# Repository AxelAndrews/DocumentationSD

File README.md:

# DocumentationSD
Documentation hub for the 2024-2025 Portal Box Senior Design project. Contains instruction guides, reports, diagrams, and other documentation related to the project.

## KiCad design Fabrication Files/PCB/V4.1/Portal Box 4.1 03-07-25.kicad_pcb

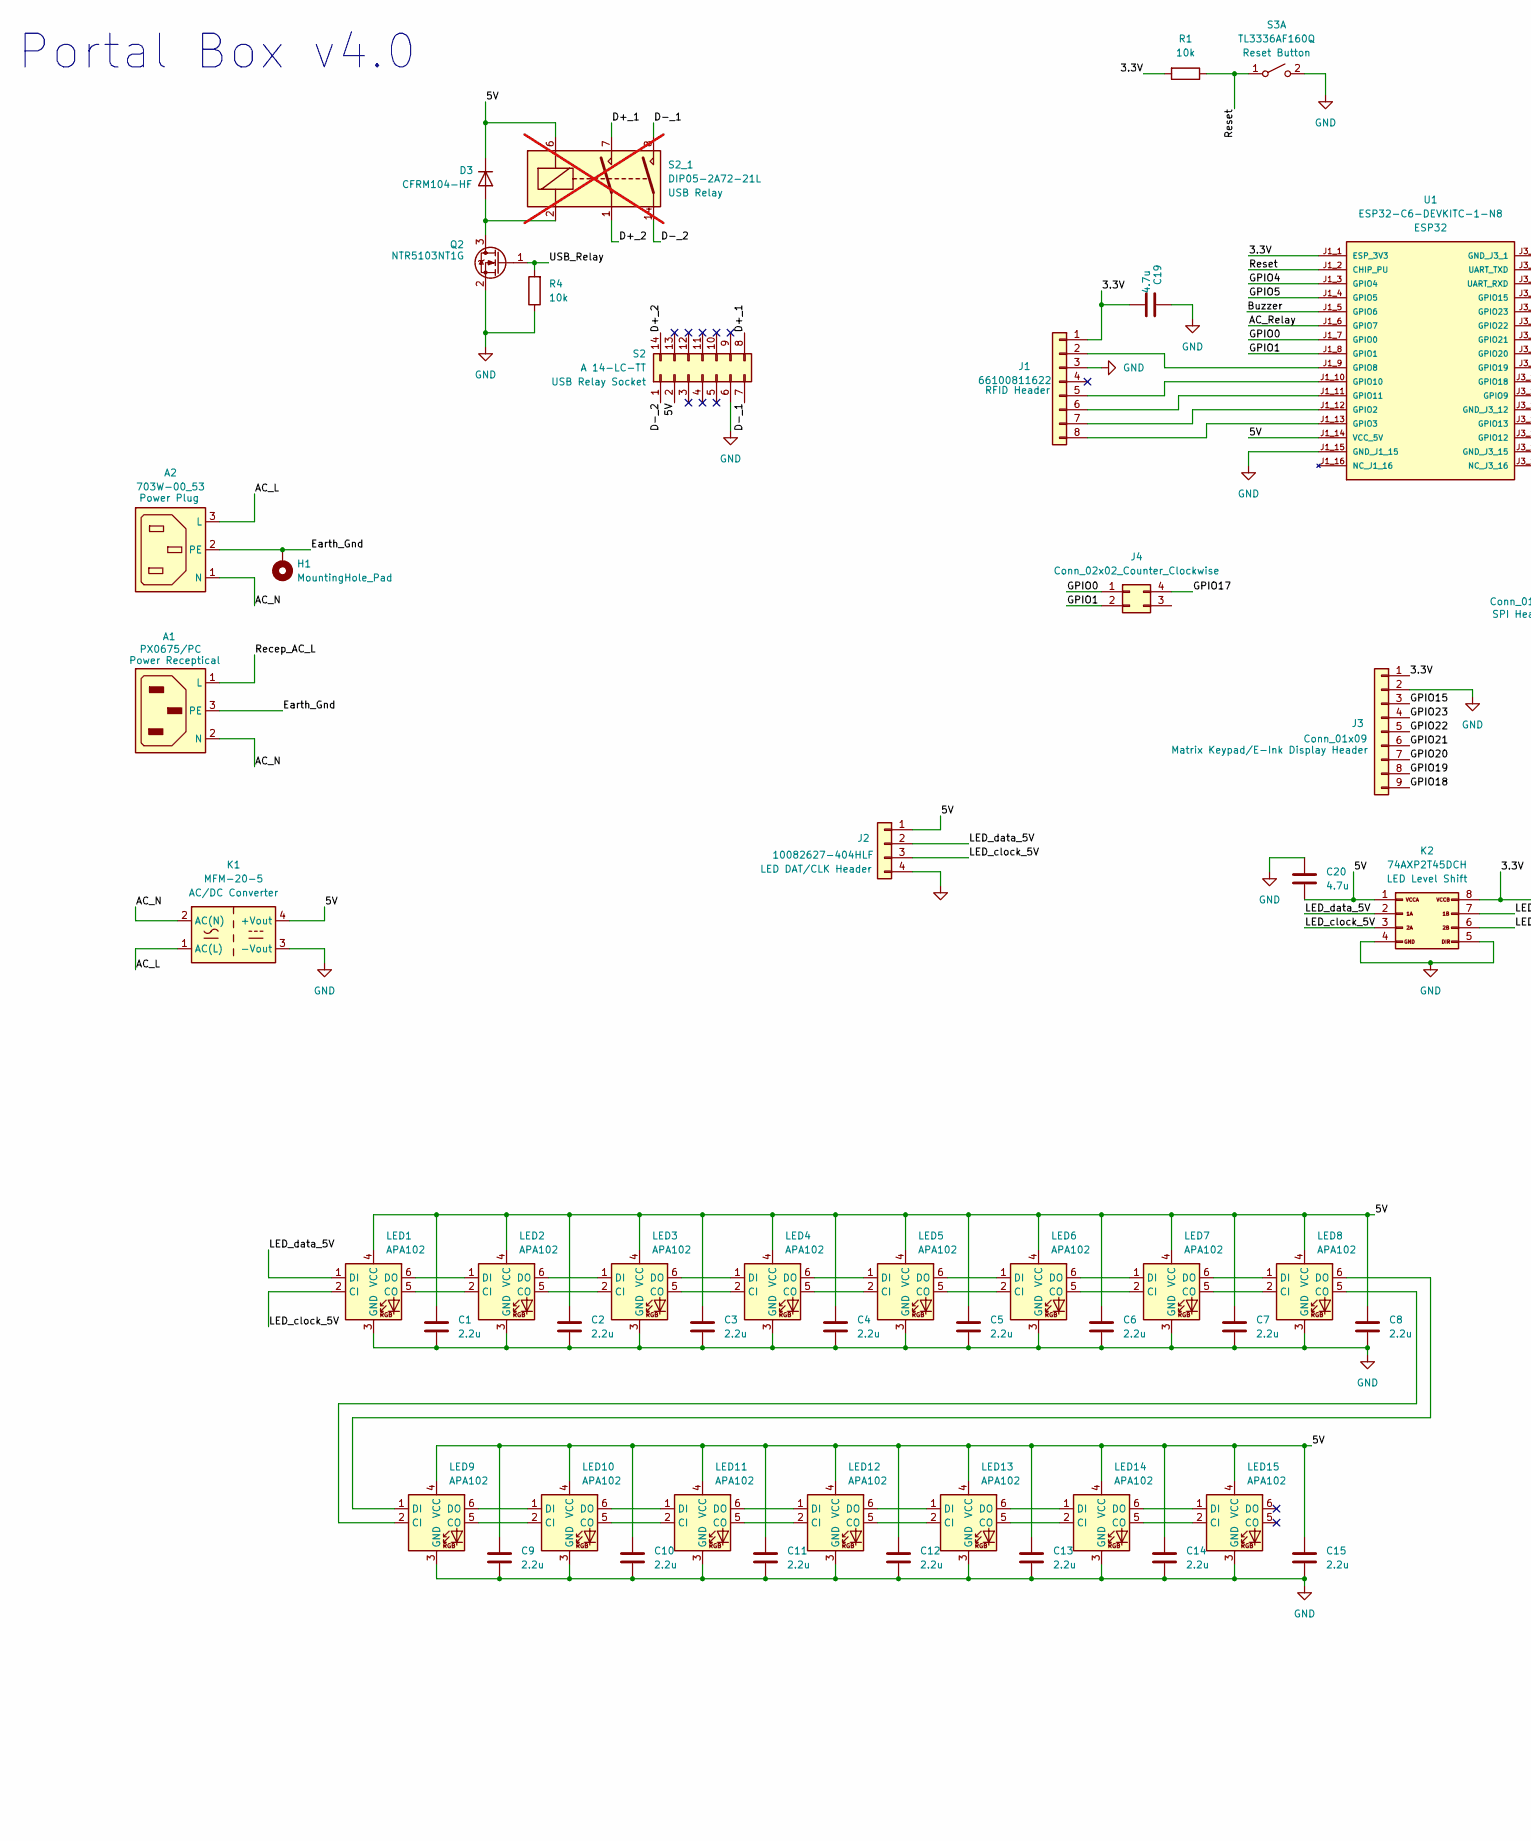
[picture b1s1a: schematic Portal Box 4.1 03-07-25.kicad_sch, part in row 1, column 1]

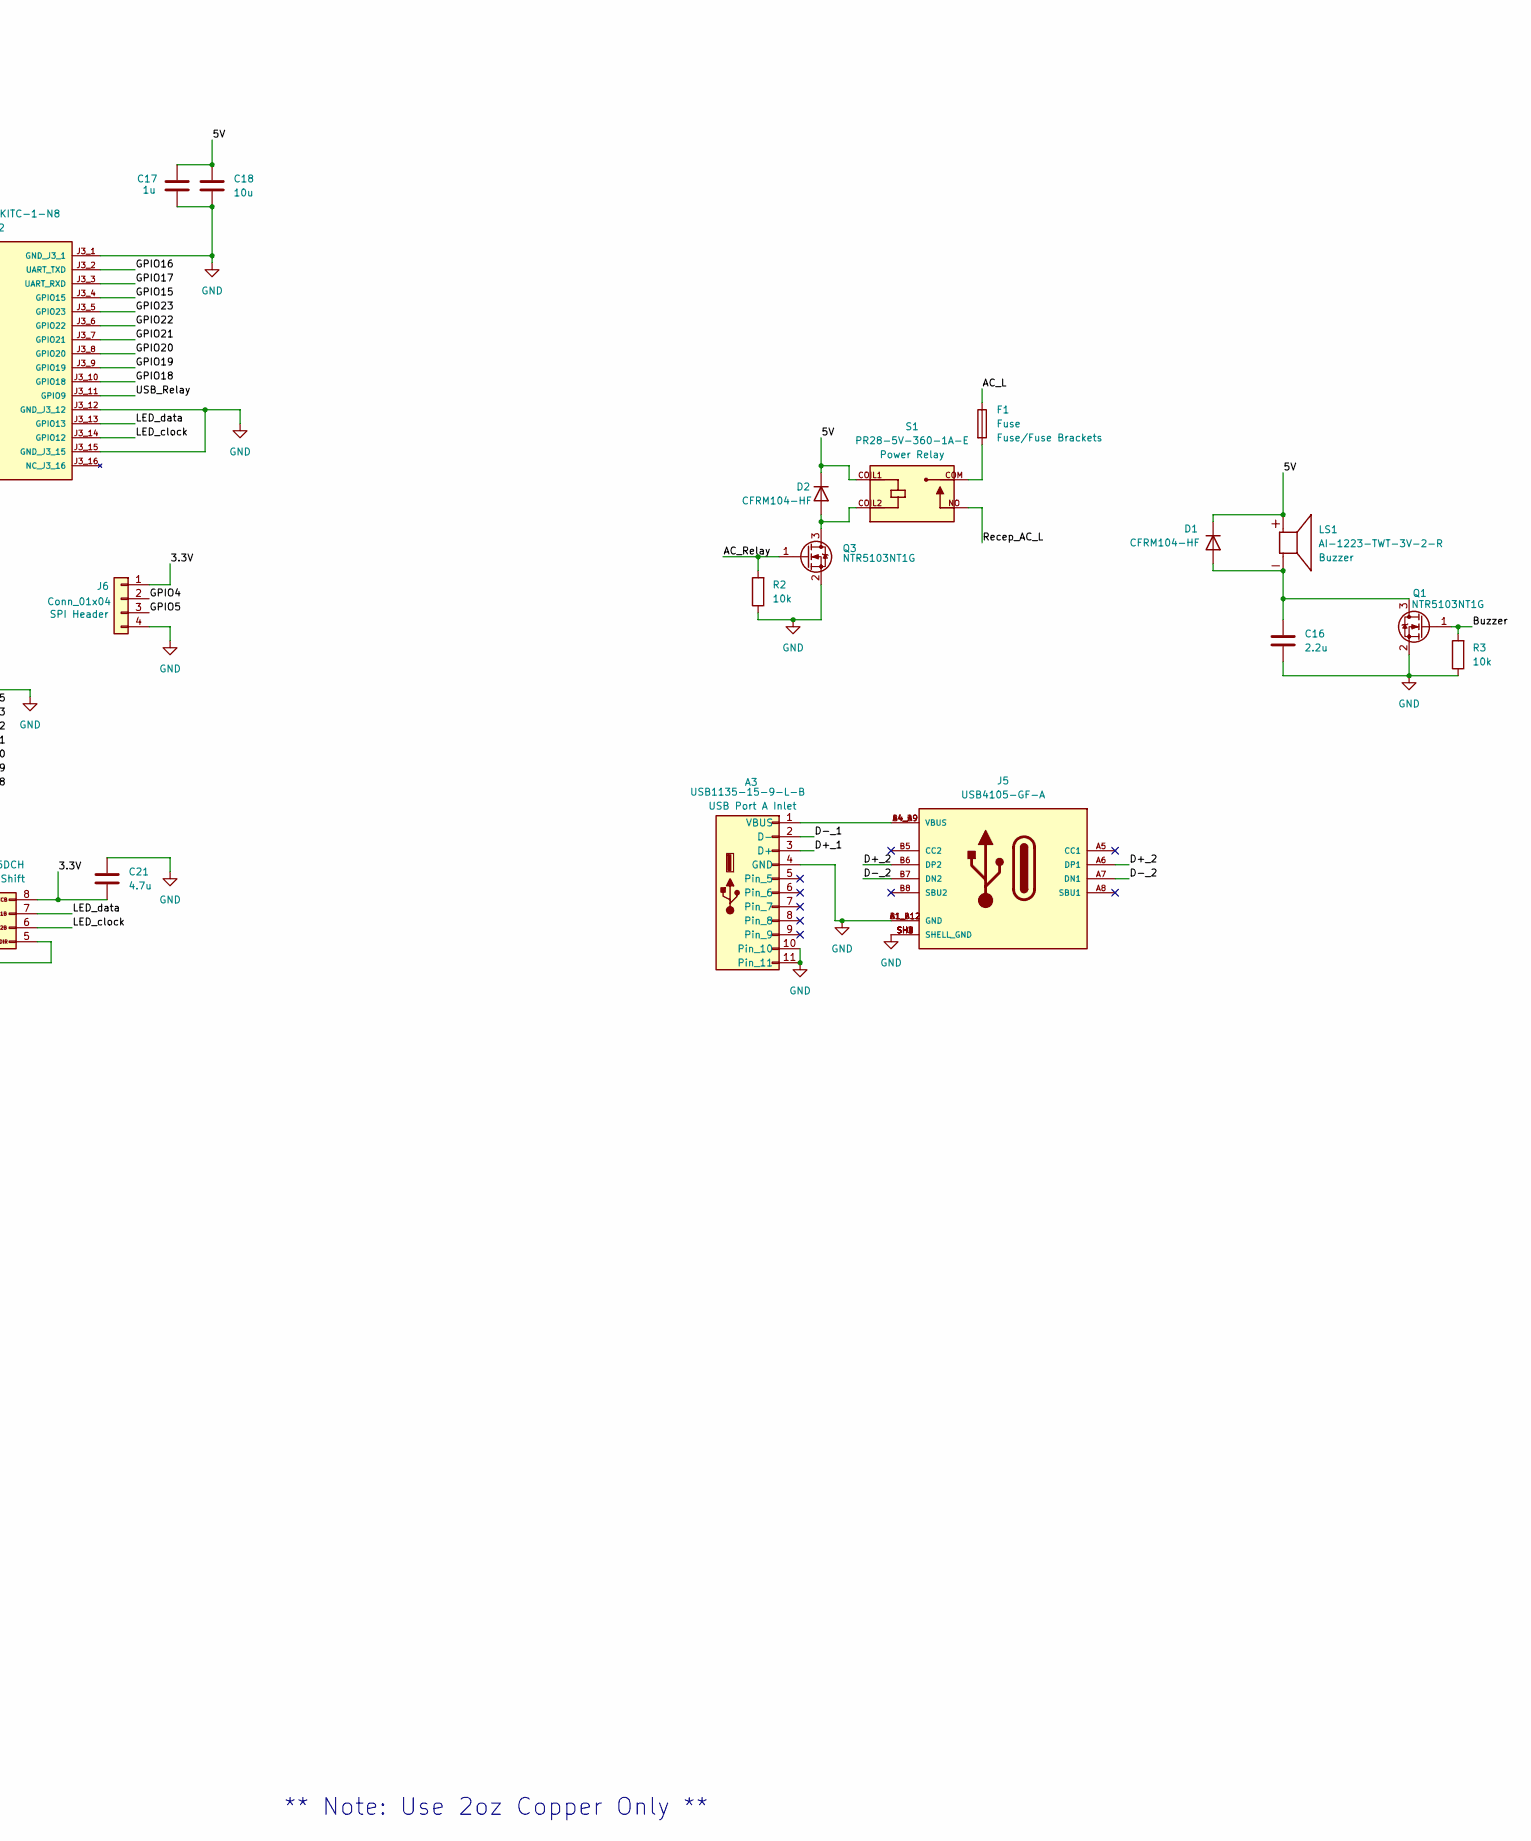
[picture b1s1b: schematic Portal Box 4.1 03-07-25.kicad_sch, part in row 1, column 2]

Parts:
A1: PX0675/PC; BULGIN_PX0675_PC
A2: 703W-00_53; QUALTEK_703W-00_53
A3: USB1135-15-9-L-B; GCT_USB1135-15-9-L-B_REVA1
C1, C2, C3, C4, C5, C6, C7, C8, C9, C10, C11, C12, C13, C14, C15, C16: 2.2u; C_0805_2012Metric
C17: 1u; C_0805_2012Metric
C18: 10u; C_0805_2012Metric
C19, C20, C21: 4.7u; C_0805_2012Metric
D1, D2, D3: CFRM104-HF; D_SOD-123
F1: Fuse; Fuseholder_Clip-5x20mm_Schurter_CQM_Inline_P20.60x5.00mm_D1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
H1: MountingHole_Pad; MountingHole_3.2mm_M3
J1: 66100811622; PinHeader_1x08_P2.54mm_Vertical
J2: 10082627-404HLF; PinHeader_1x04_P2.54mm_Vertical
J3: Conn_01x09; PinHeader_1x09_P2.54mm_Vertical
J4: Conn_02x02_Counter_Clockwise; PinHeader_2x02_P2.54mm_Vertical
J5: USB4105-GF-A; GCT_USB4105-GF-A; PARTREV B4
J6: Conn_01x04; PinHeader_1x04_P2.54mm_Vertical
K1: MFM-20-5; Converter_ACDC_MeanWell_MFM-15-xx_THT
K2: 74AXP2T45DCH; VSSOP8_SOT765-1_NEX
LED1, LED2, LED3, LED4, LED5, LED6, LED7, LED8, LED9, LED10, LED11, LED12, LED13, LED14, LED15: APA102; SK9822_ADA
LS1: AI-1223-TWT-3V-2-R; XDCR_AI-1223-TWT-3V-2-R; PARTREV 3/18/2020; DigiKey_Part_Number 668-1456-ND
Q1, Q2, Q3: NTR5103NT1G; SOT-23
R1, R2, R3, R4: 10k; R_0805_2012Metric
S1: PR28-5V-360-1A-E; RELAY_PR28-5V-360-1A-E; PARTREV 1.01
S2: A 14-LC-TT; DIP-14_W7.62mm
S2_1: DIP05-2A72-21L; Relay_StandexMeder_DIP_LowProfile; not fitted
S3: TL3336AF160Q; SW_TL3336AF160Q
U1: ESP32-C6-DEVKITC-1-N8; MODULE_ESP32-C6-DEVKITC-1-N8; PARTREV 1.3

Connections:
/3.3V: C19.2, C21.2, J1.1, J3.1, J6.1, K2.8 (VCCB), R1.2, U1.J1_1 (ESP_3V3)
/5V: C1.1, C2.1, C3.1, C4.1, C5.1, C6.1, C7.1, C8.1, C9.1, C10.1, C11.1, C12.1, C13.1, C14.1, C15.1, C17.1, C18.1, C20.2, D1.1 (K), D2.1 (K), D3.1 (K), J2.1, K1.4 (+Vout), K2.1 (VCCA), LED1.4 (VCC), LED2.4 (VCC), LED3.4 (VCC), LED4.4 (VCC), LED5.4 (VCC), LED6.4 (VCC), LED7.4 (VCC), LED8.4 (VCC), LED9.4 (VCC), LED10.4 (VCC), LED11.4 (VCC), LED12.4 (VCC), LED13.4 (VCC), LED14.4 (VCC), LED15.4 (VCC), LS1.P, S1.COIL1, S2.2, S2_1.6, U1.J1_14 (VCC_5V)
/AC_L: A2.3 (L), F1.1, K1.1 (AC(L))
/AC_N: A1.2 (N), A2.1 (N), K1.2 (AC(N))
/AC_Relay: Q3.1 (G), R2.2, U1.J1_6 (GPIO7)
/Buzzer: Q1.1 (G), R3.2, U1.J1_5 (GPIO6)
/D+_1: A3.3 (D+), S2.8, S2_1.7
/D+_2: J5.A6 (DP1), J5.B6 (DP2), S2.14, S2_1.1
/D-_1: A3.2 (D-), S2.7, S2_1.8
/D-_2: J5.A7 (DN1), J5.B7 (DN2), S2.1, S2_1.14
/Earth_Gnd: A1.3 (PE), A2.2 (PE), H1.1
/GPIO0: J4.1, U1.J1_7 (GPIO0)
/GPIO1: J4.2, U1.J1_8 (GPIO1)
/GPIO4: J6.2, U1.J1_3 (GPIO4)
/GPIO5: J6.3, U1.J1_4 (GPIO5)
/GPIO15: J3.3, U1.J3_4 (GPIO15)
/GPIO16: U1.J3_2 (UART_TXD)
/GPIO17: J4.4, U1.J3_3 (UART_RXD)
/GPIO18: J3.9, U1.J3_10 (GPIO18)
/GPIO19: J3.8, U1.J3_9 (GPIO19)
/GPIO20: J3.7, U1.J3_8 (GPIO20)
/GPIO21: J3.6, U1.J3_7 (GPIO21)
/GPIO22: J3.5, U1.J3_6 (GPIO22)
/GPIO23: J3.4, U1.J3_5 (GPIO23)
/LED_clock: K2.6 (2B), U1.J3_14 (GPIO12)
/LED_clock_5V: J2.3, K2.3 (2B), LED1.2 (CI)
/LED_data: K2.7 (1B), U1.J3_13 (GPIO13)
/LED_data_5V: J2.2, K2.2 (1A), LED1.1 (DI)
/Recep_AC_L: A1.1 (L), S1.NO
/Reset: R1.1, S3.1 (A), U1.J1_2 (CHIP_PU)
/USB_Relay: Q2.1 (G), R4.2, U1.J3_11 (GPIO9)
GND: A3.4 (GND), A3.10, A3.11, C1.2, C2.2, C3.2, C4.2, C5.2, C6.2, C7.2, C8.2, C9.2, C10.2, C11.2, C12.2, C13.2, C14.2, C15.2, C16.2, C17.2, C18.2, C19.1, C20.1, C21.1, J1.3, J2.4, J3.2, J5.A1_B12 (GND), J5.B1_A12 (GND), J5.SH1 (SHELL_GND), J5.SH2 (SHELL_GND), J5.SH3 (SHELL_GND), J5.SH4 (SHELL_GND), J6.4, K1.3 (-Vout), K2.4 (GND), K2.5 (DIR), LED1.3 (GND), LED2.3 (GND), LED3.3 (GND), LED4.3 (GND), LED5.3 (GND), LED6.3 (GND), LED7.3 (GND), LED8.3 (GND), LED9.3 (GND), LED10.3 (GND), LED11.3 (GND), LED12.3 (GND), LED13.3 (GND), LED14.3 (GND), LED15.3 (GND), Q1.2 (S), Q2.2 (S), Q3.2 (S), R2.1, R3.1, R4.1, S2.6, S3.2 (B), U1.J1_15 (GND_J1_15), U1.J3_1 (GND_J3_1), U1.J3_12 (GND_J3_12), U1.J3_15 (GND_J3_15)
unnamed: A3.1 (VBUS), J5.A4_B9 (VBUS), J5.B4_A9 (VBUS)
unnamed: C16.1, D1.2 (A), LS1.N, Q1.3 (D)
unnamed: D2.2 (A), Q3.3 (D), S1.COIL2
unnamed: D3.2 (A), Q2.3 (D), S2_1.2
unnamed: F1.2, S1.COM
unnamed: J1.2, U1.J1_9 (GPIO8)
unnamed: J1.5, U1.J1_10 (GPIO10)
unnamed: J1.6, U1.J1_11 (GPIO11)
unnamed: J1.7, U1.J1_12 (GPIO2)
unnamed: J1.8, U1.J1_13 (GPIO3)
unnamed: LED1.5 (CO), LED2.2 (CI)
unnamed: LED1.6 (DO), LED2.1 (DI)
unnamed: LED2.5 (CO), LED3.2 (CI)
unnamed: LED2.6 (DO), LED3.1 (DI)
unnamed: LED3.5 (CO), LED4.2 (CI)
unnamed: LED3.6 (DO), LED4.1 (DI)
unnamed: LED4.5 (CO), LED5.2 (CI)
unnamed: LED4.6 (DO), LED5.1 (DI)
unnamed: LED5.5 (CO), LED6.2 (CI)
unnamed: LED5.6 (DO), LED6.1 (DI)
unnamed: LED6.5 (CO), LED7.2 (CI)
unnamed: LED6.6 (DO), LED7.1 (DI)
unnamed: LED7.5 (CO), LED8.2 (CI)
unnamed: LED7.6 (DO), LED8.1 (DI)
unnamed: LED8.5 (CO), LED9.2 (CI)
unnamed: LED8.6 (DO), LED9.1 (DI)
unnamed: LED9.5 (CO), LED10.2 (CI)
unnamed: LED10.5 (CO), LED11.2 (CI)
unnamed: LED9.6 (DO), LED10.1 (DI)
unnamed: LED10.6 (DO), LED11.1 (DI)
unnamed: LED11.5 (CO), LED12.2 (CI)
unnamed: LED11.6 (DO), LED12.1 (DI)
unnamed: LED12.5 (CO), LED13.2 (CI)
unnamed: LED12.6 (DO), LED13.1 (DI)
unnamed: LED13.5 (CO), LED14.2 (CI)
unnamed: LED13.6 (DO), LED14.1 (DI)
unnamed: LED14.5 (CO), LED15.2 (CI)
unnamed: LED14.6 (DO), LED15.1 (DI)

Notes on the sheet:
** Note: Use 2oz Copper Only **
Portal Box v4.0

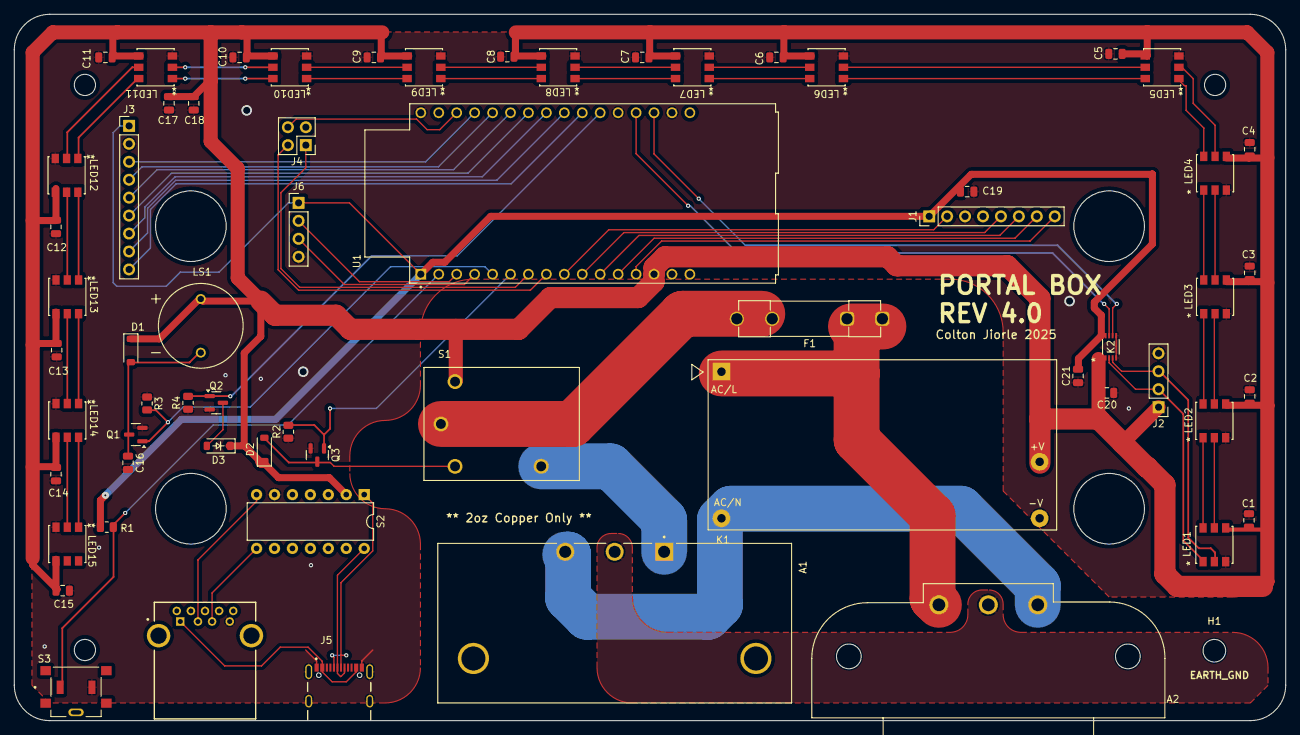
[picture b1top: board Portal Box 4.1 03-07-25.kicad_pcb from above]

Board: 2 copper layers, 180.0 x 100.0 mm, 64 parts (0 on the bottom side), 69 nets.

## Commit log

2025-05-12 Added Documentation Package
2025-05-12 Updating with large files
